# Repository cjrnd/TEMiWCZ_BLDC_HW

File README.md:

# TEMiWCZ_BLDC_HW

A BLDC driver which utilizes FOC algorithm.
<br />
<br />

### PCB

### TESTING

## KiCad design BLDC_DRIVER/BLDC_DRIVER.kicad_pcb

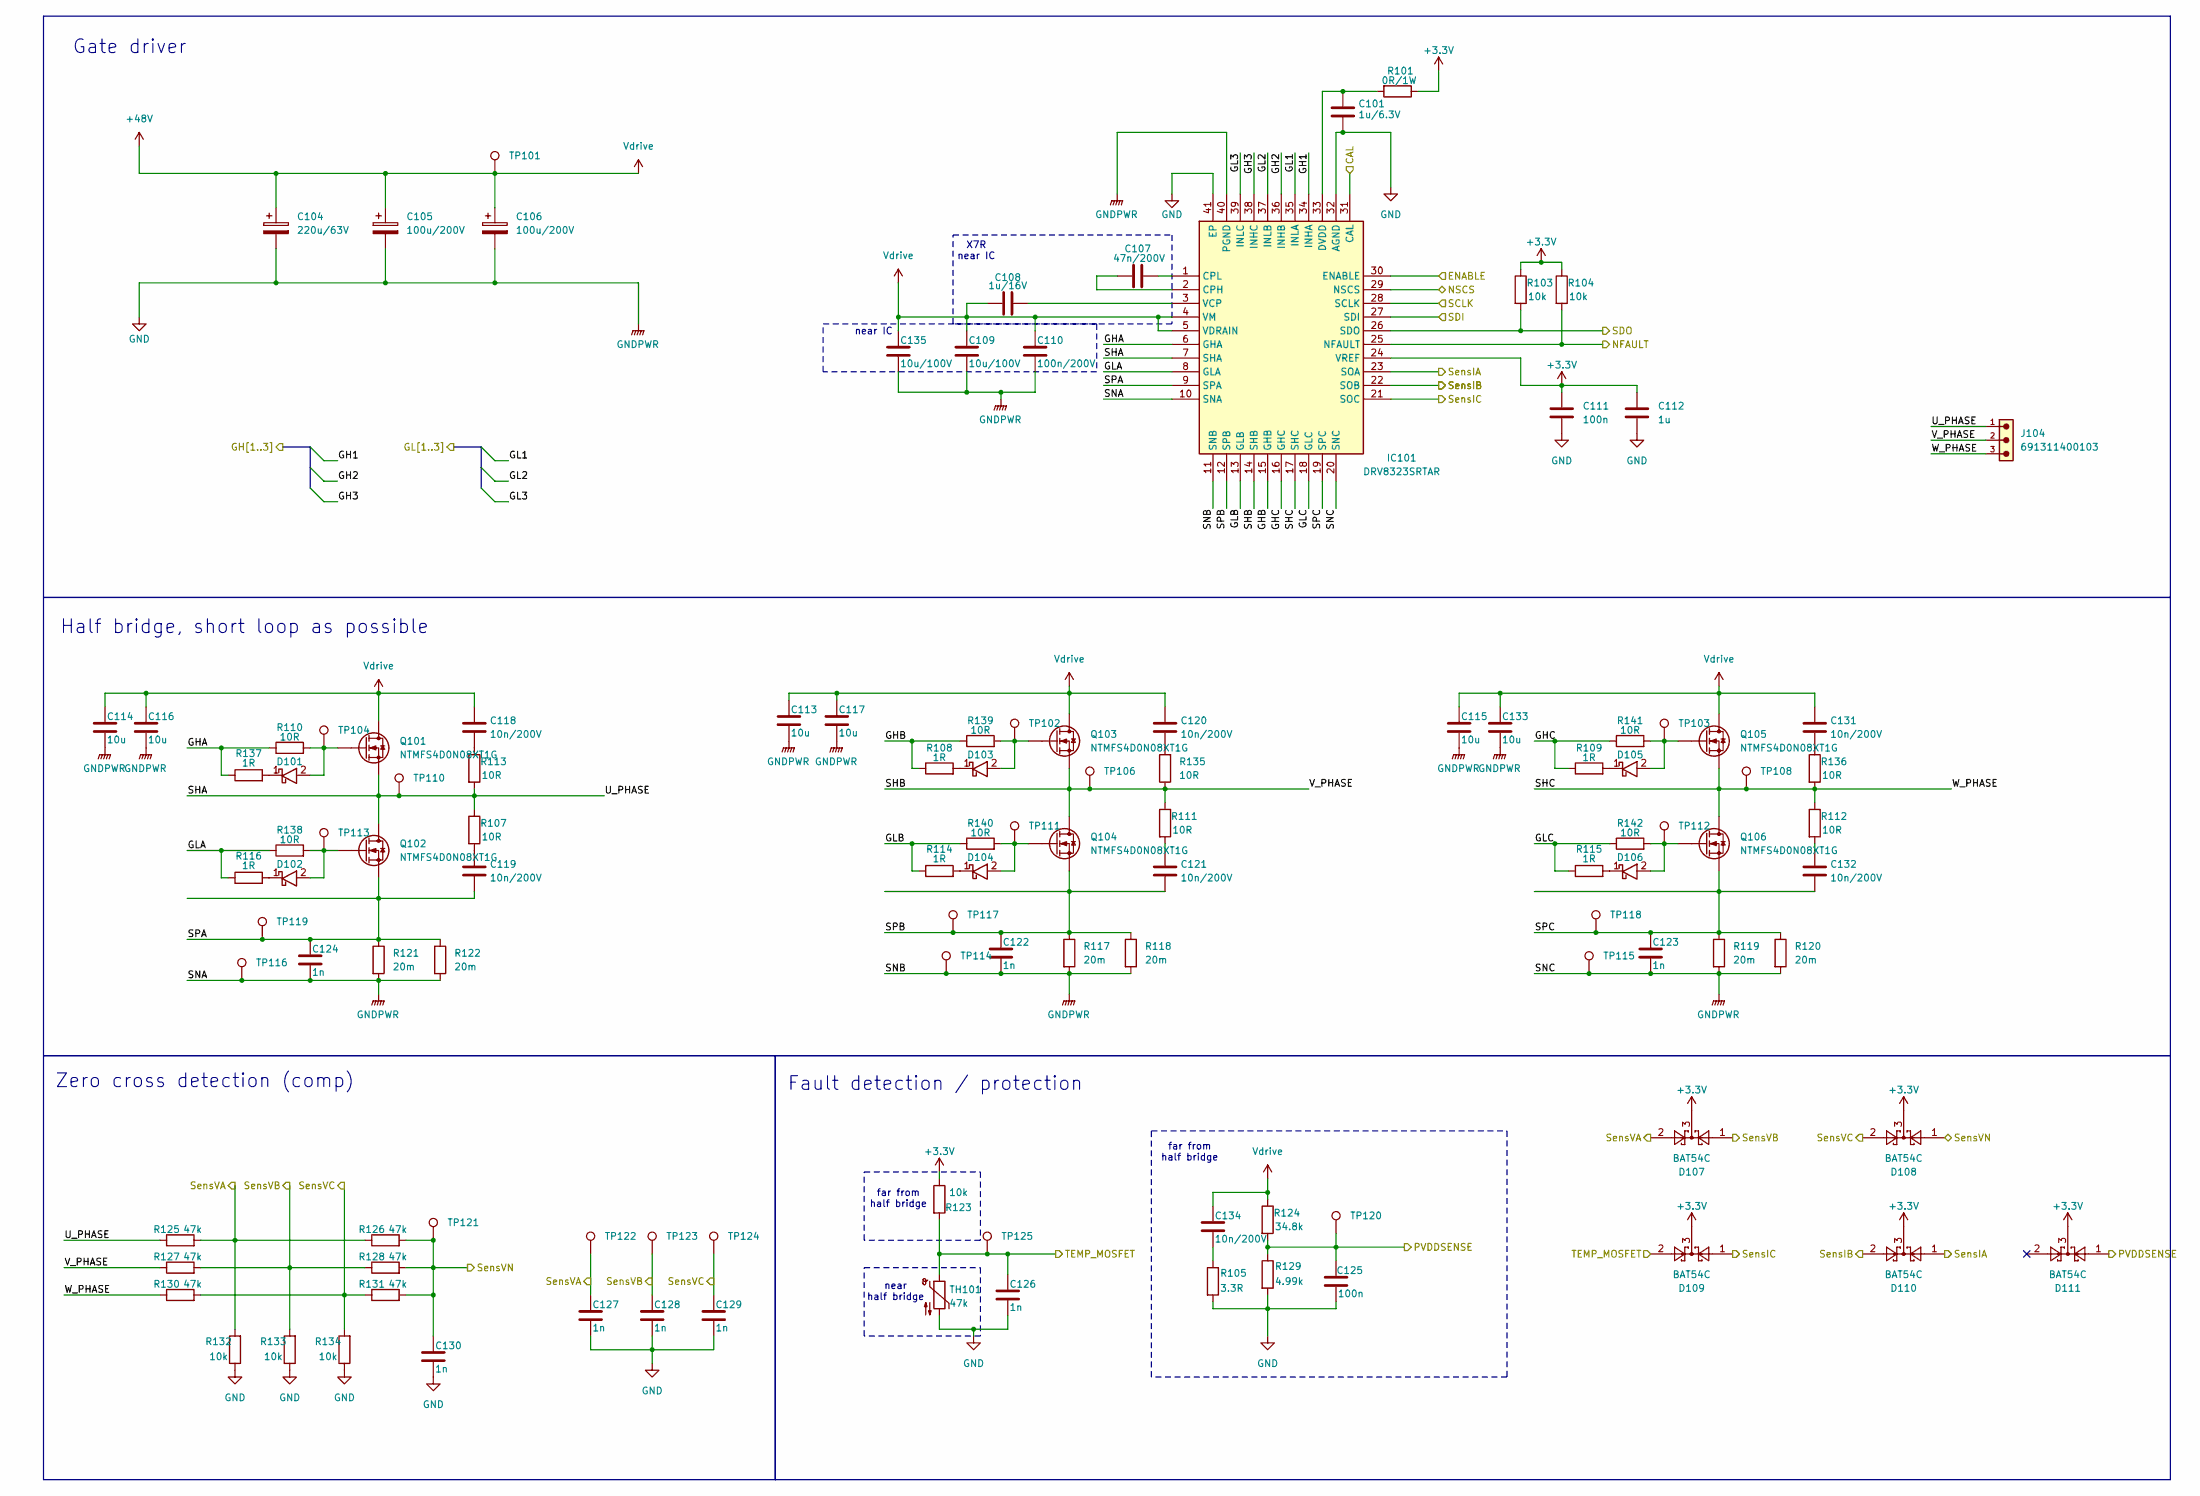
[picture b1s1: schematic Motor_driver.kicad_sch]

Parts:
C101: 1u/6.3V; C_0603_1608Metric
C104: 220u/63V; CAPAE1300X1400N
C105, C106: 100u/200V; CAPAE1300X1400N
C107: 47n/200V; C_0805_2012Metric
C108: 1u/16V; C_0805_2012Metric
C109, C135: 10u/100V; C_1210_3225Metric
C110: 100n/200V; C_0805_2012Metric
C111, C125: 100n; C_0603_1608Metric
C112: 1u; C_0805_2012Metric
C113, C114, C115, C116, C117, C133: 10u; C_1206_3216Metric
C118, C119, C120, C121, C131, C132: 10n/200V; C_1206_3216Metric
C122, C123, C124, C126, C127, C128, C129, C130: 1n; C_0603_1608Metric
C134: 10n/200V; C_0805_2012Metric
D101, D102, D103, D104, D105, D106: SBR3U60P1-7; D_PowerDI-123; Mouser Part Number 621-SBR3U60P1-7
D107, D108, D109, D110, D111: BAT54C; SOT-23
IC101: DRV8323SRTAR; QFN50P600X600X80-41N-D; Mouser Part Number 595-DRV8323SRTAR
J104: 691311400103
Q101, Q102, Q103, Q104, Q105, Q106: NTMFS4D0N08XT1G; NRVTS10100EMFST1G; Mouser Part Number 863-NTMFS4D0N08XT1G
R101: 0R/1W; R_0805_2012Metric
R103, R104, R123, R132, R133, R134: 10k; R_0603_1608Metric
R105: 3.3R; R_0805_2012Metric
R107, R110, R111, R112, R113, R135, R136, R138, R139, R140, R141, R142: 10R; R_1210_3225Metric
R108, R109, R114, R115, R116, R137: 1R; R_1210_3225Metric
R117, R118, R119, R120, R121, R122: 20m; R_2512_6332Metric
R124: 34.8k; R_0603_1608Metric
R125, R126, R127, R128, R130, R131: 47k; R_0603_1608Metric
R129: 4.99k; R_0603_1608Metric
TH101: 47k; R_0603_1608Metric
TP101, TP102, TP103, TP104, TP106, TP108, TP110, TP111, TP112, TP113, TP114, TP115, TP116, TP117, TP118, TP119, TP120, TP121, TP122, TP123, TP124, TP125: TestPoint; TestPoint_Pad_D1.5mm

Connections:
+3.3V: C111.1, C112.1, D107.3, D108.3, D109.3, D110.3, D111.3, IC101.24 (VREF), R101.1, R103.1, R104.1, R123.1; also elsewhere on the board
+48V: C104.1, C105.1, C106.1, C108.1, C109.1, C110.1, C113.1, C114.1, C115.1, C116.1, C117.1, C118.1, C120.1, C131.1, C133.1, C134.1, C135.1, IC101.4 (VM), IC101.5 (VDRAIN), Q101.5, Q103.5, Q105.5, R124.1, TP101.1; also elsewhere on the board
/MCU/CAL: IC101.31 (CAL); also elsewhere on the board
/MCU/ENABLE: IC101.30 (ENABLE); also elsewhere on the board
/MCU/GH1: IC101.34 (INHA); also elsewhere on the board
/MCU/GH2: IC101.36 (INHB); also elsewhere on the board
/MCU/GH3: IC101.38 (INHC); also elsewhere on the board
/MCU/GL1: IC101.35 (INLA); also elsewhere on the board
/MCU/GL2: IC101.37 (INLB); also elsewhere on the board
/MCU/GL3: IC101.39 (INLC); also elsewhere on the board
/MCU/NFAULT: IC101.25 (NFAULT), R104.2; also elsewhere on the board
/MCU/NSCS: IC101.29 (NSCS); also elsewhere on the board
/MCU/PVDDSENSE: C125.1, D111.1, R124.2, R129.1, TP120.1; also elsewhere on the board
/MCU/SCLK: IC101.28 (SCLK); also elsewhere on the board
/MCU/SDI: IC101.26 (SDO), R103.2; also elsewhere on the board
/MCU/SDO: IC101.27 (SDI); also elsewhere on the board
/MCU/SensIA: D110.1, IC101.23 (SOA); also elsewhere on the board
/MCU/SensIB: D110.2, IC101.22 (SOB); also elsewhere on the board
/MCU/SensIC: D109.1, IC101.21 (SOC); also elsewhere on the board
/MCU/SensVA: C127.1, D107.2, R125.2, R126.1, R132.2, TP122.1; also elsewhere on the board
/MCU/SensVB: C128.1, D107.1, R127.2, R128.1, R133.2, TP123.1; also elsewhere on the board
/MCU/SensVC: C129.1, D108.2, R130.2, R131.1, R134.2, TP124.1; also elsewhere on the board
/MCU/SensVN: C130.1, D108.1, R126.2, R128.2, R131.2, TP121.1; also elsewhere on the board
/MCU/TEMP_MOSFET: C126.1, D109.2, R123.2, TH101.1, TP125.1; also elsewhere on the board
/Motor_driver/GHA: IC101.6 (GHA), R110.1, R137.1
/Motor_driver/GHB: IC101.15 (GHB), R108.1, R139.1
/Motor_driver/GHC: IC101.16 (GHC), R109.1, R141.1
/Motor_driver/GLA: IC101.8 (GLA), R116.1, R138.1
/Motor_driver/GLB: IC101.13 (GLB), R114.1, R140.1
/Motor_driver/GLC: IC101.18 (GLC), R115.1, R142.1
/Motor_driver/SHA: IC101.7 (SHA), J104.1, Q101.1, Q102.5, R107.1, R113.2, R125.1, TP110.1
/Motor_driver/SHB: IC101.14 (SHB), J104.2, Q103.1, Q104.5, R111.1, R127.1, R135.1, TP106.1
/Motor_driver/SHC: IC101.17 (SHC), J104.3, Q105.1, Q106.5, R112.1, R130.1, R136.2, TP108.1
/Motor_driver/SPA: C119.2, C124.1, IC101.9 (SPA), Q102.1, R121.1, R122.1, TP119.1
/Motor_driver/SPB: C121.2, C122.1, IC101.12 (SPB), Q104.1, R117.1, R118.1, TP117.1
/Motor_driver/SPC: C123.1, C132.2, IC101.19 (SPC), Q106.1, R119.1, R120.1, TP118.1
GND: C101.2, C104.2, C105.2, C106.2, C109.2, C110.2, C111.2, C112.2, C113.2, C114.2, C115.2, C116.2, C117.2, C122.2, C123.2, C124.2, C125.2, C126.2, C127.2, C128.2, C129.2, C130.2, C133.2, C135.2, IC101.10 (SNA), IC101.11 (SNB), IC101.20 (SNC), IC101.32 (AGND), IC101.40 (PGND), IC101.41 (EP), R105.2, R117.2, R118.2, R119.2, R120.2, R121.2, R122.2, R129.2, R132.1, R133.1, R134.1, TH101.2, TP114.1, TP115.1, TP116.1; also elsewhere on the board
unnamed: C118.2, R113.1
unnamed: C119.1, R107.2
unnamed: C120.2, R135.2
unnamed: C121.1, R111.2
unnamed: C131.2, R136.1
unnamed: C132.1, R112.2
unnamed: C134.2, R105.1
unnamed: D101.1, R137.2
unnamed: D101.2, Q101.4, R110.2, TP104.1
unnamed: D102.1, R116.2
unnamed: D102.2, Q102.4, R138.2, TP113.1
unnamed: D103.1, R108.2
unnamed: D103.2, Q103.4, R139.2, TP102.1
unnamed: D104.1, R114.2
unnamed: D104.2, Q104.4, R140.2, TP111.1
unnamed: D105.1, R109.2
unnamed: D105.2, Q105.4, R141.2, TP103.1
unnamed: D106.1, R115.2
unnamed: D106.2, Q106.4, R142.2, TP112.1
unnamed: C107.1, IC101.2 (CPH)
unnamed: C107.2, IC101.1 (CPL)
unnamed: C101.1, IC101.33 (DVDD), R101.2
unnamed: C108.2, IC101.3 (VCP)

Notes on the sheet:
Fault detection / protection
Gate driver
far from half bridge
X7R near IC
Zero cross detection (comp)
near half bridge
near IC
Half bridge, short loop as possible

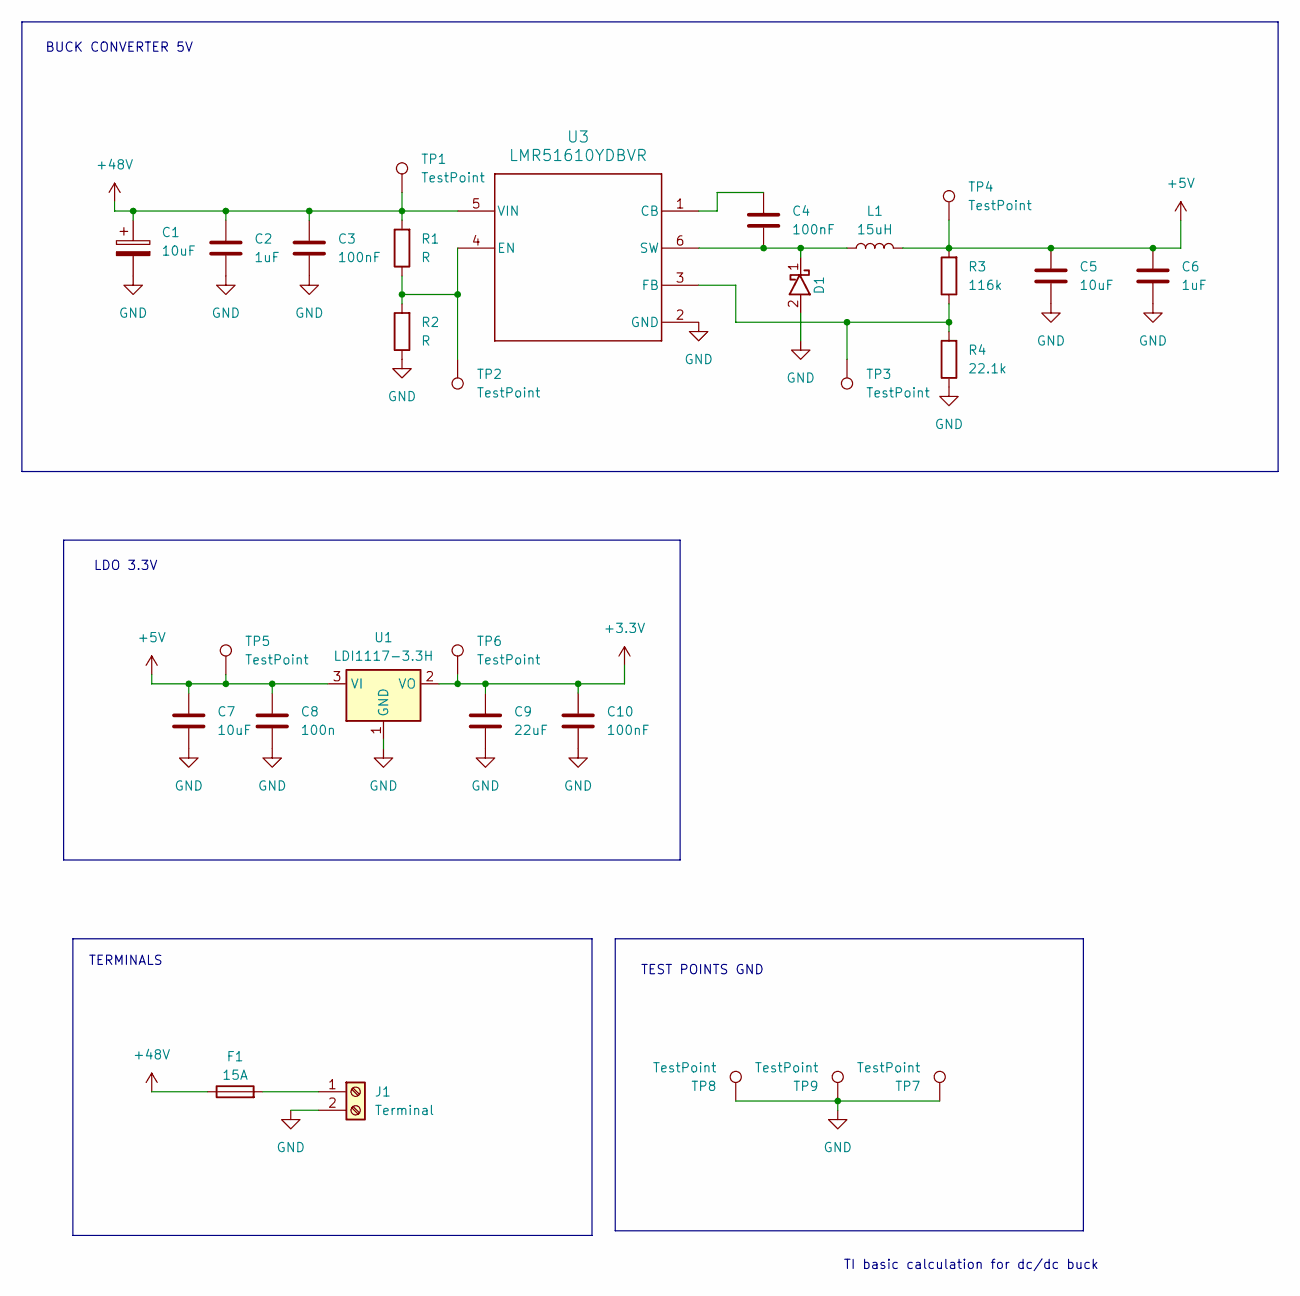
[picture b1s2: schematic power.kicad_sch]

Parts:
C1, C5, C7: 10uF; C_0805_2012Metric_Pad1.18x1.45mm_HandSolder
C2, C6: 1uF; C_0805_2012Metric_Pad1.18x1.45mm_HandSolder
C3, C10: 100nF; C_0805_2012Metric_Pad1.18x1.45mm_HandSolder
C4: 100nF; C_0603_1608Metric_Pad1.08x0.95mm_HandSolder
C8: 100n; C_0603_1608Metric_Pad1.08x0.95mm_HandSolder
C9: 22uF; C_0805_2012Metric_Pad1.18x1.45mm_HandSolder
D1: SBR3U60P1-7; D_PowerDI-123; Mouser Part Number 621-SBR3U60P1-7
F1: 15A; Fuse_Blade_Mini_directSolder
J1: Terminal; TerminalBlock_Wuerth_691311400102_P7.62mm
L1: 15uH; L_APV_ANR6045
R1, R2: R; R_0603_1608Metric_Pad0.98x0.95mm_HandSolder
R3: 116k; R_0603_1608Metric_Pad0.98x0.95mm_HandSolder
R4: 22.1k; R_0603_1608Metric_Pad0.98x0.95mm_HandSolder
TP1, TP2, TP3, TP4, TP5, TP6, TP7, TP8, TP9: TestPoint; TestPoint_Pad_D1.5mm
U1: LDI1117-3.3H; SOT-223-3_TabPin2
U3: LMR51610YDBVR; SOT-23-6

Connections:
+3.3V: C9.1, C10.1, TP6.1, U1.2 (VO); also elsewhere on the board
+5V: C5.2, C6.2, C7.1, C8.1, L1.2, R3.2, TP4.1, TP5.1, U1.3 (VI)
+48V: C1.1, C2.1, C3.2, F1.1, R1.2, TP1.1, U3.5 (VIN); also elsewhere on the board
GND: C1.2, C2.2, C3.1, C5.1, C6.1, C7.2, C8.2, C9.2, C10.2, D1.2, J1.2, R2.1, R4.1, TP7.1, TP8.1, TP9.1, U1.1 (GND), U3.2 (GND); also elsewhere on the board
unnamed: F1.2, J1.1
unnamed: C4.2, U3.1 (CB)
unnamed: R1.1, R2.2, TP2.1, U3.4 (EN)
unnamed: R3.1, R4.2, TP3.1, U3.3 (FB)
unnamed: C4.1, D1.1, L1.1, U3.6 (SW)

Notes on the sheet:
LDO 3.3V
TEST POINTS GND
BUCK CONVERTER 5V
TI basic calculation for dc/dc buck
TERMINALS

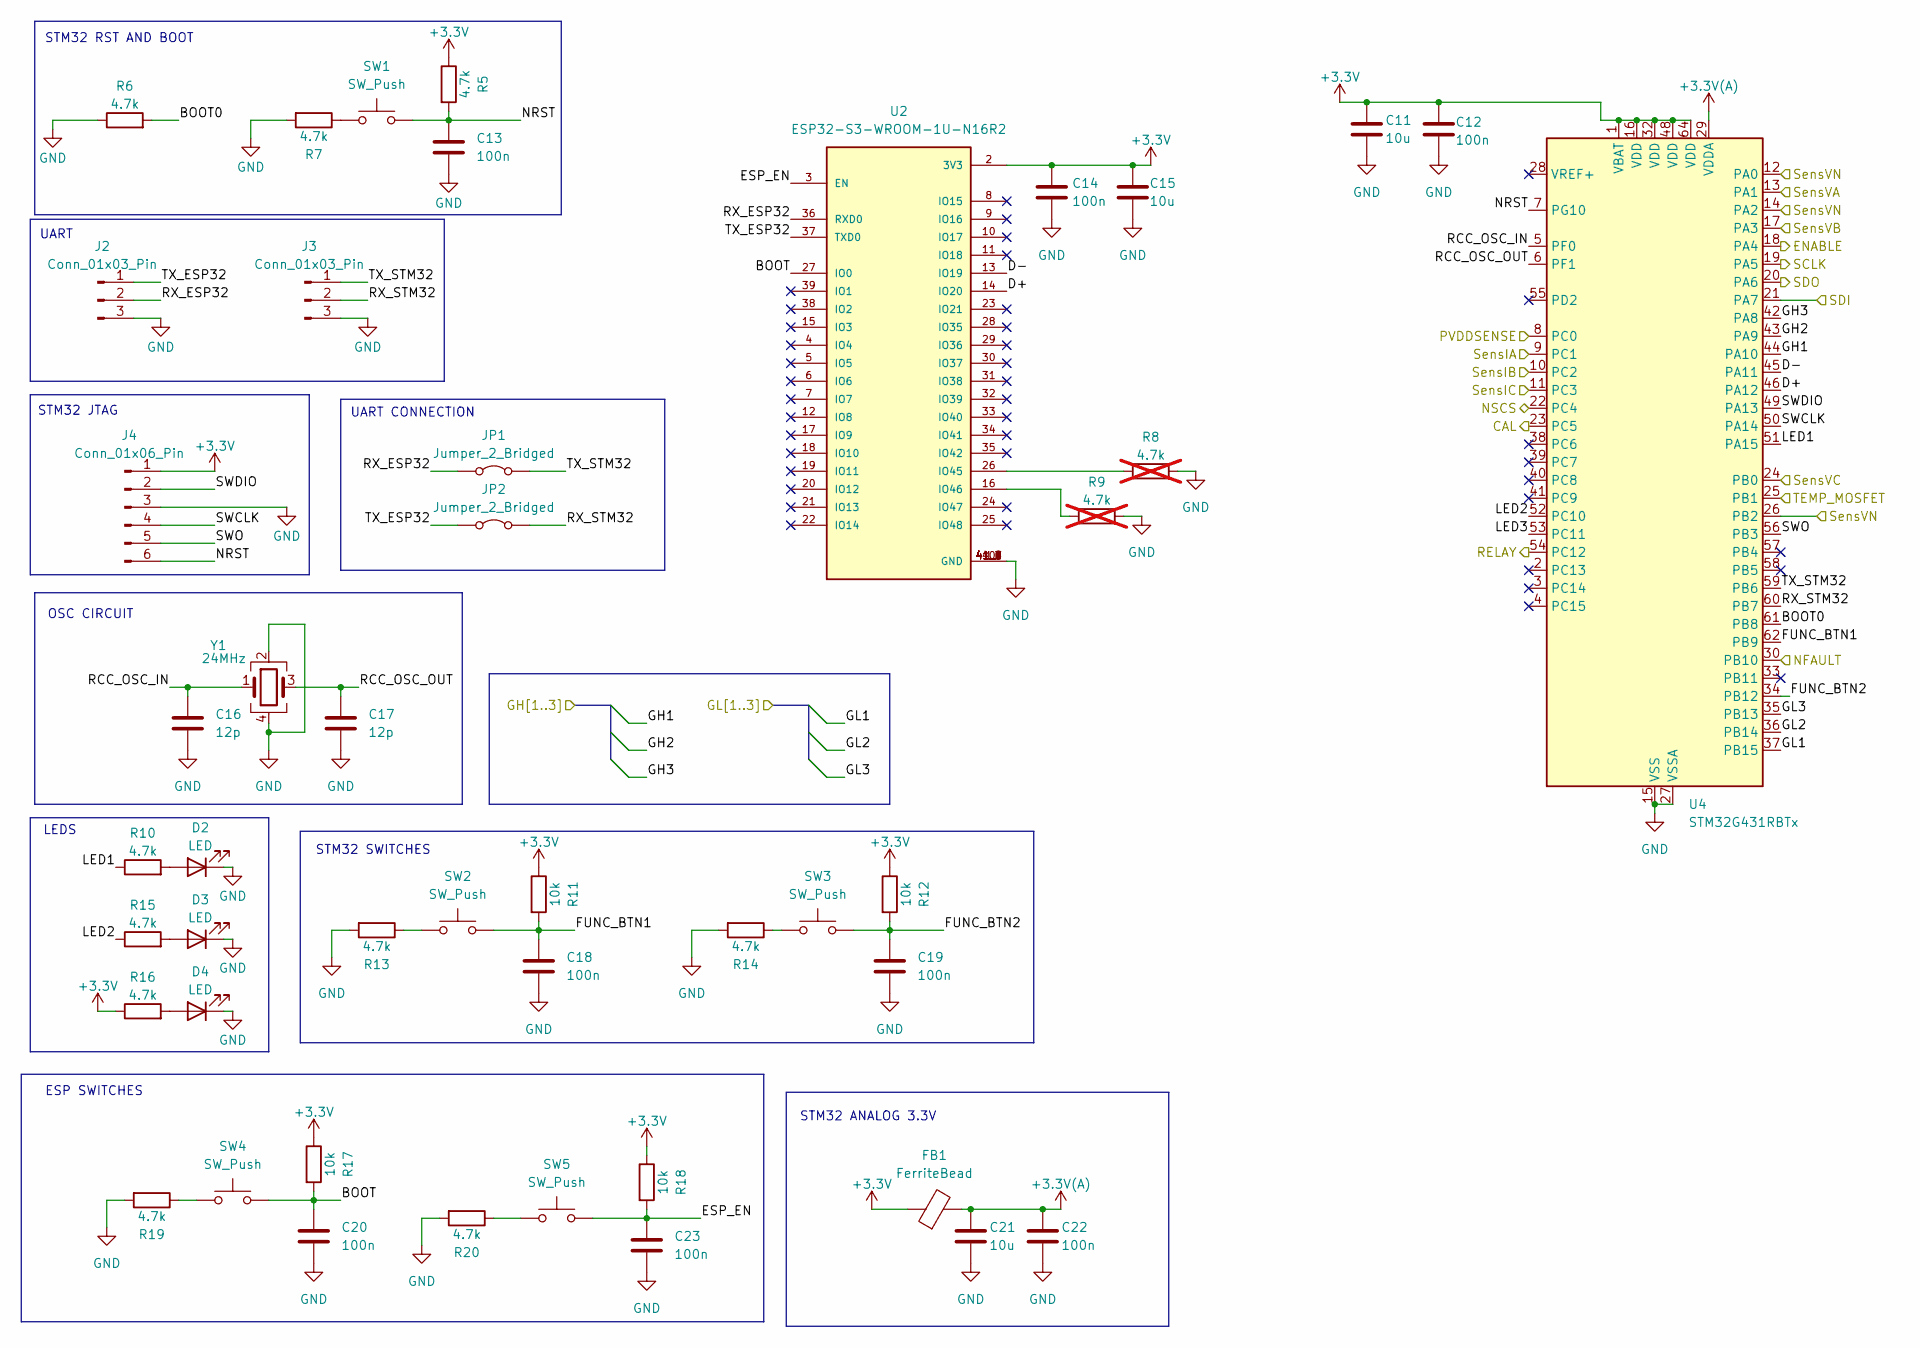
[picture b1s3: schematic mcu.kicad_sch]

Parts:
C11, C15, C21: 10u; C_0603_1608Metric_Pad1.08x0.95mm_HandSolder
C12, C13, C14, C18, C19, C20, C22, C23: 100n; C_0603_1608Metric_Pad1.08x0.95mm_HandSolder
C16, C17: 12p; C_0603_1608Metric_Pad1.08x0.95mm_HandSolder
D2, D3, D4: LED; D_0805_2012Metric_Pad1.15x1.40mm_HandSolder
FB1: FerriteBead; L_0805_2012Metric_Pad1.05x1.20mm_HandSolder
J2, J3: Conn_01x03_Pin; PinHeader_1x03_P2.54mm_Vertical
J4: Conn_01x06_Pin; PinHeader_1x06_P2.54mm_Vertical
JP1, JP2: Jumper_2_Bridged; SolderJumper-2_P1.3mm_Open_TrianglePad1.0x1.5mm
R5, R6, R7, R10, R13, R14, R15, R16, R19, R20: 4.7k; R_0603_1608Metric_Pad0.98x0.95mm_HandSolder
R8, R9: 4.7k; R_0603_1608Metric; not fitted
R11, R12, R17, R18: 10k; R_0603_1608Metric_Pad0.98x0.95mm_HandSolder
SW1, SW2, SW3, SW4, SW5: SW_Push; SW_Tactile_SPST_NO_Straight_CK_PTS636Sx25SMTRLFS
U2: ESP32-S3-WROOM-1U-N16R2; XCVR_ESP32-S3-WROOM-1U-N16R2; PARTREV v1.1
U4: STM32G431RBTx; LQFP-64_10x10mm_P0.5mm
Y1: 24MHz; Crystal_SMD_3225-4Pin_3.2x2.5mm

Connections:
+3.3V: C11.2, C12.2, C14.2, C15.2, FB1.1, J4.1, R5.1, R11.1, R12.1, R16.1, R17.1, R18.1, U2.2 (3V3), U4.1 (VBAT), U4.16 (VDD), U4.32 (VDD), U4.48 (VDD), U4.64 (VDD); also elsewhere on the board
+3.3V(A): C21.2, C22.2, FB1.2, U4.29 (VDDA)
/MCU/BOOT: C20.2, R17.2, SW4.2, U2.27 (IO0)
/MCU/BOOT0: R6.2, U4.61 (PB8)
/MCU/CAL: U4.23 (PC5); also elsewhere on the board
/MCU/D+: U2.14 (IO20), U4.46 (PA12)
/MCU/D-: U2.13 (IO19), U4.45 (PA11)
/MCU/ENABLE: U4.18 (PA4); also elsewhere on the board
/MCU/ESP_EN: C23.2, R18.2, SW5.2, U2.3 (EN)
/MCU/FUNC_BTN1: C18.2, R11.2, SW2.2, U4.62 (PB9)
/MCU/FUNC_BTN2: C19.2, R12.2, SW3.2, U4.34 (PB12)
/MCU/GH1: U4.44 (PA10); also elsewhere on the board
/MCU/GH2: U4.43 (PA9); also elsewhere on the board
/MCU/GH3: U4.42 (PA8); also elsewhere on the board
/MCU/GL1: U4.37 (PB15); also elsewhere on the board
/MCU/GL2: U4.36 (PB14); also elsewhere on the board
/MCU/GL3: U4.35 (PB13); also elsewhere on the board
/MCU/LED1: R10.1, U4.51 (PA15)
/MCU/LED2: R15.1, U4.52 (PC10)
/MCU/LED3: U4.53 (PC11)
/MCU/NFAULT: U4.30 (PB10); also elsewhere on the board
/MCU/NRST: C13.2, J4.6, R5.2, SW1.2, U4.7 (PG10)
/MCU/NSCS: U4.22 (PC4); also elsewhere on the board
/MCU/PVDDSENSE: U4.8 (PC0); also elsewhere on the board
/MCU/RCC_OSC_IN: C16.2, U4.5 (PF0), Y1.1
/MCU/RCC_OSC_OUT: C17.2, U4.6 (PF1), Y1.3
/MCU/RELAY: U4.54 (PC12)
/MCU/RX_ESP32: J2.2, JP1.1 (A), U2.36 (RXD0)
/MCU/RX_STM32: J3.2, JP2.2 (B), U4.60 (PB7)
/MCU/SCLK: U4.19 (PA5); also elsewhere on the board
/MCU/SDI: U4.21 (PA7); also elsewhere on the board
/MCU/SDO: U4.20 (PA6); also elsewhere on the board
/MCU/SWCLK: J4.4, U4.50 (PA14)
/MCU/SWDIO: J4.2, U4.49 (PA13)
/MCU/SWO: J4.5, U4.56 (PB3)
/MCU/SensIA: U4.9 (PC1); also elsewhere on the board
/MCU/SensIB: U4.10 (PC2); also elsewhere on the board
/MCU/SensIC: U4.11 (PC3); also elsewhere on the board
/MCU/SensVA: U4.13 (PA1); also elsewhere on the board
/MCU/SensVB: U4.17 (PA3); also elsewhere on the board
/MCU/SensVC: U4.24 (PB0); also elsewhere on the board
/MCU/SensVN: U4.12 (PA0), U4.14 (PA2), U4.26 (PB2); also elsewhere on the board
/MCU/TEMP_MOSFET: U4.25 (PB1); also elsewhere on the board
/MCU/TX_ESP32: J2.1, JP2.1 (A), U2.37 (TXD0)
/MCU/TX_STM32: J3.1, JP1.2 (B), U4.59 (PB6)
GND: C11.1, C12.1, C13.1, C14.1, C15.1, C16.1, C17.1, C18.1, C19.1, C20.1, C21.1, C22.1, C23.1, D2.1 (K), D3.1 (K), D4.1 (K), J2.3, J3.3, J4.3, R6.1, R7.2, R8.2, R9.2, R13.2, R14.2, R19.2, R20.2, U2.1 (GND), U2.40 (GND), U2.41_1 (GND), U2.41_2 (GND), U2.41_3 (GND), U2.41_4 (GND), U2.41_5 (GND), U2.41_6 (GND), U2.41_7 (GND), U2.41_8 (GND), U2.41_9 (GND), U2.41_10, U2.41_11, U2.41_12, U2.41_13, U2.41_14, U2.41_15, U2.41_16, U2.41_17, U2.41_18, U2.41_19, U2.41_20, U2.41_21, U4.15 (VSS), U4.27 (VSSA), U4.31 (VSS), U4.47 (VSS), U4.63 (VSS), Y1.2, Y1.4; also elsewhere on the board
unnamed: D2.2 (A), R10.2
unnamed: D3.2 (A), R15.2
unnamed: D4.2 (A), R16.2
unnamed: R7.1, SW1.1
unnamed: R13.1, SW2.1
unnamed: R14.1, SW3.1
unnamed: R19.1, SW4.1
unnamed: R20.1, SW5.1
unnamed: R8.1, U2.26 (IO45)
unnamed: R9.1, U2.16 (IO46)

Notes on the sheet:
OSC CIRCUIT
LEDS
STM32 RST AND BOOT
UART
STM32 JTAG
ESP SWITCHES
UART CONNECTION
STM32 ANALOG 3.3V
STM32 SWITCHES

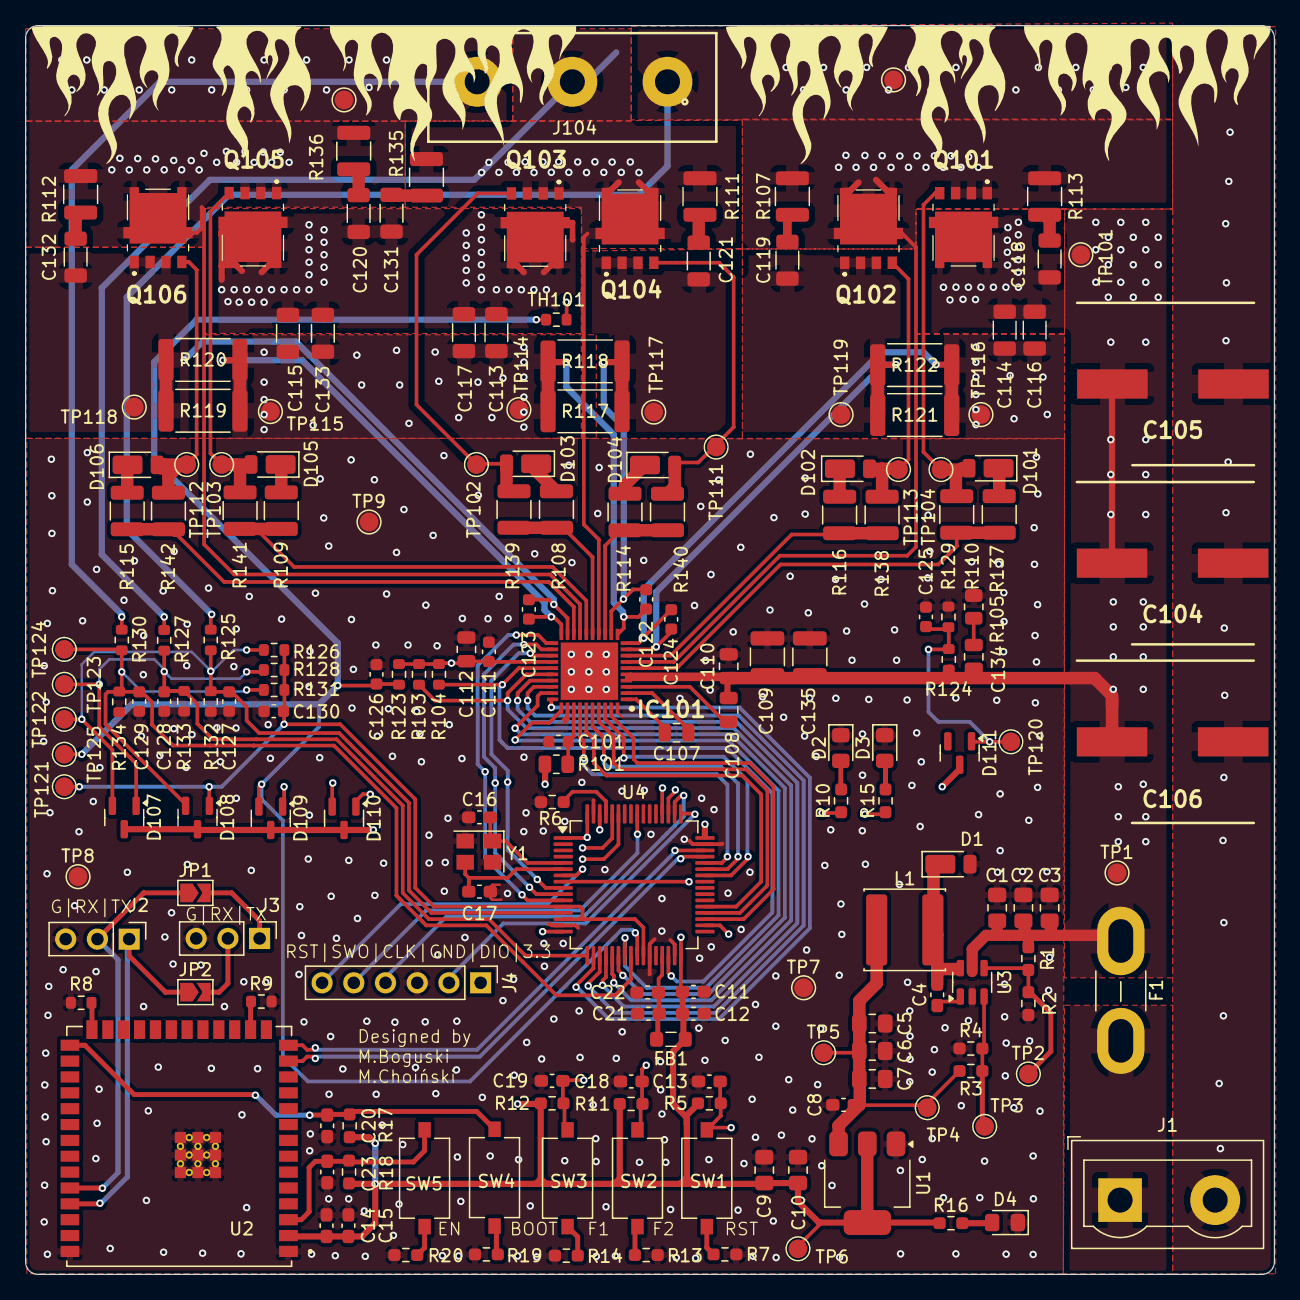
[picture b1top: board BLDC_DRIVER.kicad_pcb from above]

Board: 4 copper layers, 100.0 x 100.0 mm, 190 parts (1 on the bottom side), 96 nets.

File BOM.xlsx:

Reference | Qty | Value | Footprint | Datasheet | comment | Kolumna1 | LINK
C122,C123,C124,C126,C127,C128,C129,C130 | 8 | 1n | Capacitor_SMD:C_0603_1608Metric | ~ | CEJRO
C101 | 1 | 1u/6.3V | Capacitor_SMD:C_0603_1608Metric | ~ | CEJRO
C8,C12,C13,C14,C18,C19,C20,C22,C23 | 12 | 100n | Capacitor_SMD:C_0603_1608Metric_Pad1.08x0.95mm_HandSolder | ~ | CEJRO
C11,C15,C21 | 3 | 10u | Capacitor_SMD:C_0603_1608Metric_Pad1.08x0.95mm_HandSolder | ~ | CEJRO
C16,C17 | 2 | 12p | Capacitor_SMD:C_0603_1608Metric_Pad1.08x0.95mm_HandSolder | ~ | CEJRO
C110 | 3 | 100n/200V | Capacitor_SMD:C_0805_2012Metric | ~ | MOUSER |  | https://www.mouser.pl/ProductDetail/Samsung-Electro-Mechanic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
C108 | 3 | 1u/16V | Capacitor_SMD:C_0805_2012Metric | ~ | MOUSER |  | https://www.mouser.pl/ProductDetail/Wurth-Elektronik/8850122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
C107 | 1 | 47n/200V | Capacitor_SMD:C_0805_2012Metric | https://www.mouser.pl/ProductDetail/Walsin/0805B473K201CT?qs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 | MOUSER |  | https://www.mouser.pl/ProductDetail/Walsin/SH21B473K101CT?qs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
C1,C5,C7 | 3 | 10uF | Capacitor_SMD:C_0805_2012Metric_Pad1.18x1.45mm_HandSolder | ~ | CERO
C9 | 1 | 22uF | Capacitor_SMD:C_0805_2012Metric_Pad1.18x1.45mm_HandSolder | ~ | MOUSER |  | https://www.mouser.pl/ProductDetail/Samsung-Electro-Mechanic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
C118,C119,C120,C121,C131,C132 | 6 | 10n/200V | Capacitor_SMD:C_1206_3216Metric | ~ | CEJRO
C113,C114,C115,C116,C117,C133 | 8 | 10u/200V | Capacitor_SMD:C_1206_3216Metric | ~ | MOUSER |  | https://www.mouser.pl/ProductDetail/Walsin/1210B475K101CT?qs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
C105,C106 | 2 | 100u/200V | EMVY101ARA101MKE0S:CAPAE1300X1400N | ~ | MOUSER |  | https://www.mouser.pl/ProductDetail/KYOCERA-AVX/AEF1213221M0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
C104 | 1 | 220u/63V | EMVY101ARA101MKE0S:CAPAE1300X1400N | https://www.mouser.pl/ProductDetail/KYOCERA-AVX/AEF1213221M0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 | MOUSER |  | https://www.mouser.pl/ProductDetail/KYOCERA-AVX/AEF1213221M0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
D1,D101,D102,D103,D104,D105,D106 | 7 | SBR3U60P1-7 | Diode_SMD:D_PowerDI-123 | https://www.diodes.com//assets/Datasheets/SBR3U60P1.pdf | MOUSER |  | https://www.mouser.pl/ProductDetail/Diodes-Incorporated/SBR3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
D107,D108,D109,D110,D111 | 5 | BAT54C | Package_TO_SOT_SMD:SOT-23 | http://www.diodes.com/_files/datasheets/ds11005.pdf | MOUSER |  | https://www.mouser.pl/ProductDetail/Diotec-Semiconductor/BAT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
D2,D3,D4 | 3 | LED | Diode_SMD:D_0805_2012Metric_Pad1.15x1.40mm_HandSolder | ~ | CEJRO
F1 | 1 | 15A | Fuse:Fuse_Blade_Mini_directSolder | ~ | SKLEP
FB1 | 1 | FerriteBead | Inductor_SMD:L_0805_2012Metric_Pad1.05x1.20mm_HandSolder | ~ | CEJRO
IC101 | 1 | DRV8323SRTAR | DRV8323:QFN50P600X600X80-41N-D | http://www.ti.com/lit/ds/symlink/drv8323.pdf | MOUSER |  | https://www.mouser.pl/ProductDetail/Texas-Instruments/DRV832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
J1 | 1 | Terminal | TerminalBlock:TerminalBlock_Wuerth_691311400102_P7.62mm | ~ | Fuse_Blade_Mini_directSolder
J104 | 1 | 691311400103 | 691311400103:691311400103 |  | MOUSER |  | https://www.mouser.pl/ProductDetail/Wurth-Elektronik/6913114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
J2 J3 J4 | 3 | GOLD PIN | Connector_PinHeader_2.54mm:PinHeader_1x06_P2.54mm_Vertical | ~ | CEJRO/TY
L1 | 1 | 15uH | Inductor_SMD:L_APV_ANR6045 | https://www.mouser.pl/ProductDetail/TDK/VLS6045EX-150M?qs=oF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 | MOUSER |  | https://www.mouser.pl/ProductDetail/TDK/VLS6045EX-150M?qs=oF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
Q101,Q102,Q103,Q104,Q105,Q106 | 6 | NTMFS4D0N08XT1G | NRVTS10100EMFST1G | https://www.onsemi.com/pub/Collateral/NTMFS4D0N08X-D.PDF | MOUSER |  | https://www.mouser.pl/ProductDetail/onsemi/NTMFS4D0N08XT1G?q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
R103,R104,R123,R132,R133,R134 | 12 | 10k | Resistor_SMD:R_0603_1608Metric | ~ | CEJRO
R124 | 1 | 34.8k | Resistor_SMD:R_0603_1608Metric | ~ | MOUSER |  | https://www.mouser.pl/ProductDetail/KOA-Speer/RN73H1JTTD3482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
R8,R9 | 12 | 4.7k | Resistor_SMD:R_0603_1608Metric | ~ | CEJRO
R129 | 1 | 4.99k | Resistor_SMD:R_0603_1608Metric | ~ | MOUSER |  | https://www.mouser.pl/ProductDetail/KOA-Speer/RN73H1JTTD4991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
R125,R126,R127,R128,R130,R131,TH101 | 7 | 47k | Resistor_SMD:R_0603_1608Metric | https://www.mouser.pl/ProductDetail/Vishay-BC-Components/NTC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 | CEJRO | MOUSER
R3 | 1 | 116k | Resistor_SMD:R_0603_1608Metric_Pad0.98x0.95mm_HandSolder | ~ | MOUSER |  | https://www.mouser.pl/ProductDetail/Kamaya/RMC1-16K47R0FTP?q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
R4 | 1 | 22.1k | Resistor_SMD:R_0603_1608Metric_Pad0.98x0.95mm_HandSolder | ~ | MOUSER |  | https://www.mouser.pl/ProductDetail/Panasonic/ERJ-3EKF2212V?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
R101 | 1 | 0R/1W | Resistor_SMD:R_0805_2012Metric | ~ | MOUSER |  | chuj
R105 | 1 | 3.3R | Resistor_SMD:R_0805_2012Metric | ~ | MOUSER |  | chuj
R107,R110,R111,R112,R113,R135,R136,R138,R139,R140,R141,R142 | 12 | 10R | Resistor_SMD:R_1210_3225Metric | ~ | CEJRO
R108,R109,R114,R115,R116,R137 | 6 | 1R | Resistor_SMD:R_1210_3225Metric | ~ | CEJRO
R117,R118,R119,R120,R121,R122 | 6 | 20m | Resistor_SMD:R_2512_6332Metric | ~ | MOUSER |  | https://www.mouser.pl/ProductDetail/Ohmite/PCS2512DR0200ET?q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
SW1,SW2,SW3,SW4,SW5 | 5 | SW_Push | Button_Switch_SMD:SW_Tactile_SPST_NO_Straight_CK_PTS636Sx25SMTRLFS | ~ | MOUSER |  | https://www.mouser.pl/ProductDetail/CK/PTS636SK50JSMTR-LFS?q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
U1 | 1 | LDI1117-3.3H | Package_TO_SOT_SMD:SOT-223-3_TabPin2 | https://www.tme.eu/Document/084a5eb18462203f10c4803bc35208f3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 | CEJRO
U2 | 1 | ESP32-S3-WROOM-1U-N16R2 | ESP32-S3-WROOM-1U-N16R2:XCVR_ESP32-S3-WROOM-1U-N16R2 |  | MOUSER |  | https://www.mouser.pl/ProductDetail/Espressif-Systems/ESP32-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
U3 | 1 | LMR51610YDBVR | Package_TO_SOT_SMD:SOT-23-6 | LMR51610YDBVR | MOUSER |  | https://www.mouser.pl/ProductDetail/Texas-Instruments/LMR516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
U4 | 1 | STM32G431RBTx | Package_QFP:LQFP-64_10x10mm_P0.5mm | https://www.st.com/resource/en/datasheet/stm32g431rb.pdf | MOUSER |  | chuj
Y1 | 1 | 24MHz | Crystal:Crystal_SMD_3225-4Pin_3.2x2.5mm | https://www.tme.eu/pl/details/3225-24m-sr/rezonatory-kwarcow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 | MOUSER |  | https://www.mouser.pl/ProductDetail/CTS-Electronic-Component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

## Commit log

2025-03-26 init
2025-03-26 buck and mcu added
2025-03-30 added gate driver and igbt's
2025-03-31 BEMF measurement
2025-04-01 ldo added
2025-04-05 new driver
2025-04-06 added footprints, fault detection and temperature calc
2025-04-08 spice model
2025-04-09 mcu added
2025-04-09 snuber, removing spice
2025-04-09 footprints added, cap values corrected
2025-04-10 buck changed and calculated
2025-04-11 fuses and missing footprints added, labels cleaned
2025-04-12 new mosfet and power connector
2025-04-12 finall motor driver
2025-04-12 pcb update
2025-04-12 board constraints added
2025-04-14 pre layout
2025-04-14 motor driver layout v1
2025-04-16 via update
2025-04-16 esp/stm/ldo layout
2025-04-17 mcu&power final layout
2025-04-18 finnall layout
2025-04-21 bom + pdf
2025-08-05 pictures added
